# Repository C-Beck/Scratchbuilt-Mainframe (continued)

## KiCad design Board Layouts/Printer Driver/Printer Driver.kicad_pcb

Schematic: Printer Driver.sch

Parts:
C1, C2: 47p; C_Rect_L4.0mm_W2.5mm_P2.50mm
C3: 100n; C_Rect_L4.0mm_W2.5mm_P2.50mm
C4: 470u; CP_Radial_D8.0mm_P3.50mm
C5, C6, C7, C8: 10n; C_Rect_L4.0mm_W2.5mm_P2.50mm
D1, D2: LED; LED_D5.0mm
J1: USB_B; USB_B_OST_USB-B1HSxx_Horizontal
J2: Conn_01x06; PinHeader_1x06_P2.54mm_Vertical
J3: Conn_01x03; JST_VH_B3PS-VH_1x03_P3.96mm_Horizontal
J4: DB25_Female_MountingHoles; DSUB-25_Female_Horizontal_P2.77x2.84mm_EdgePinOffset9.90mm_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
J5: 8P8C; RJ45_Amphenol_54602-x08_Horizontal
R1: 4k7; R_Axial_DIN0207_L6.3mm_D2.5mm_P10.16mm_Horizontal
R2: 10k; R_Axial_DIN0207_L6.3mm_D2.5mm_P10.16mm_Horizontal
R3, R4: 27; R_Axial_DIN0207_L6.3mm_D2.5mm_P10.16mm_Horizontal
R5, R6: 270; R_Axial_DIN0207_L6.3mm_D2.5mm_P10.16mm_Horizontal
R7, R8: 2k; R_Axial_DIN0207_L6.3mm_D2.5mm_P10.16mm_Horizontal
R9, R11, R12, R14: 600; R_Axial_DIN0207_L6.3mm_D2.5mm_P10.16mm_Horizontal
R10, R13: 120; R_Axial_DIN0207_L6.3mm_D2.5mm_P10.16mm_Horizontal
U1: FT230XS; SSOP-16_3.9x4.9mm_P0.635mm
U2: PIC16F1503-IP; DIP-14_W7.62mm_Socket
U3: 74HC595; DIP-16_W7.62mm
U4: PCA9615; TSSOP-10_3x3mm_P0.5mm

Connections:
+5V: C4.1, C5.1, C6.1, C7.1, C8.1, J2.2, J3.1, R7.2, R8.2, R9.1, R12.1, U1.12 (VCC), U2.1 (VDD), U3.10 (~SRCLR), U3.16 (VCC), U4.1, U4.10
GND: C1.2, C2.2, C3.2, C4.2, C5.2, C6.2, C7.2, C8.2, J1.4 (GND), J2.3, J3.3, J4.18, J4.19, J4.20, J4.21, J4.22, J4.23, J4.24, J4.25, R2.2, R11.2, R14.2, U1.5 (GND), U1.13 (GND), U2.14 (VSS), U3.8 (GND), U3.13 (~OE), U4.5
unnamed: C1.1, J1.2 (D-), R3.2
unnamed: C2.1, J1.3 (D+), R4.2
unnamed: C3.1, D1.2 (A), D2.2 (A), U1.3 (VCCIO), U1.10 (3V3OUT), U1.11 (~RESET)
unnamed: D1.1 (K), R5.1
unnamed: D2.1 (K), R6.1
unnamed: J1.1 (VBUS), R1.1
unnamed: J2.1, U2.4 (RA3/T1G/CLC1IN0/~SS~/~MCLR~/Vpp)
unnamed: J2.4, J4.1, U2.13 (RA0/AN0/DACOUT1/C1IN+/ICSPDAT)
unnamed: J2.5, U1.1 (TXD), U2.12 (RA1/AN1/Vref+/C1IN0-/C2IN0-/ICSPCLK)
unnamed: J4.2, U3.15 (QA)
unnamed: J4.3, U3.1 (QB)
unnamed: J4.4, U3.2 (QC)
unnamed: J4.5, U3.3 (QD)
unnamed: J4.6, U3.4 (QE)
unnamed: J4.7, U3.5 (QF)
unnamed: J4.8, U3.6 (QG)
unnamed: J4.9, U3.7 (QH)
unnamed: J4.11, U2.5 (PWM1/CLC1/CWG1A/RC5)
unnamed: J5.1, R10.2, R11.1, U4.9
unnamed: J5.2, R9.2, R10.1, U4.8
unnamed: J5.7, R13.2, R14.1, U4.6
unnamed: J5.8, R12.2, R13.1, U4.7
unnamed: R1.2, R2.1, U1.16 (CBUS3)
unnamed: R3.1, U1.9 (USBDM)
unnamed: R4.1, U1.8 (USBDP)
unnamed: R5.2, U1.14 (CBUS1)
unnamed: R6.2, U1.7 (CBUS2)
unnamed: R7.1, U2.10 (SCK/SCL/CLC2/C2IN+/AN4/RC0), U4.4
unnamed: R8.1, U2.9 (SDI/SDA/PWM4/NCO1/C2IN1-/C1IN1-/AN5/RC1), U4.2
unnamed: U1.2 (~RTS), U2.3 (RA4/AN3/T1G/NCO1/SDO/CLKOUT)
unnamed: U1.4 (RXD), U2.11 (RA2/AN2/DACOUT2/C1OUT/T0CKI/~CWG1FLT~/C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)
unnamed: U1.6 (~CTS), U2.2 (RA5/T1CKI/NCO1CLK/CLCIN1/CLKIN)
unnamed: U2.6 (CLC2IN1/CWG1B/C2OUT/RC4), U3.12 (RCLK)
unnamed: U2.7 (~SS~/PWM2/CLCIN0/C2IN3-/C1IN3-/AN7/RC3), U3.11 (SRCLK)
unnamed: U2.8 (SDO/C2IN2-/C1IN2-/AN6/RC2), U3.14 (SER)

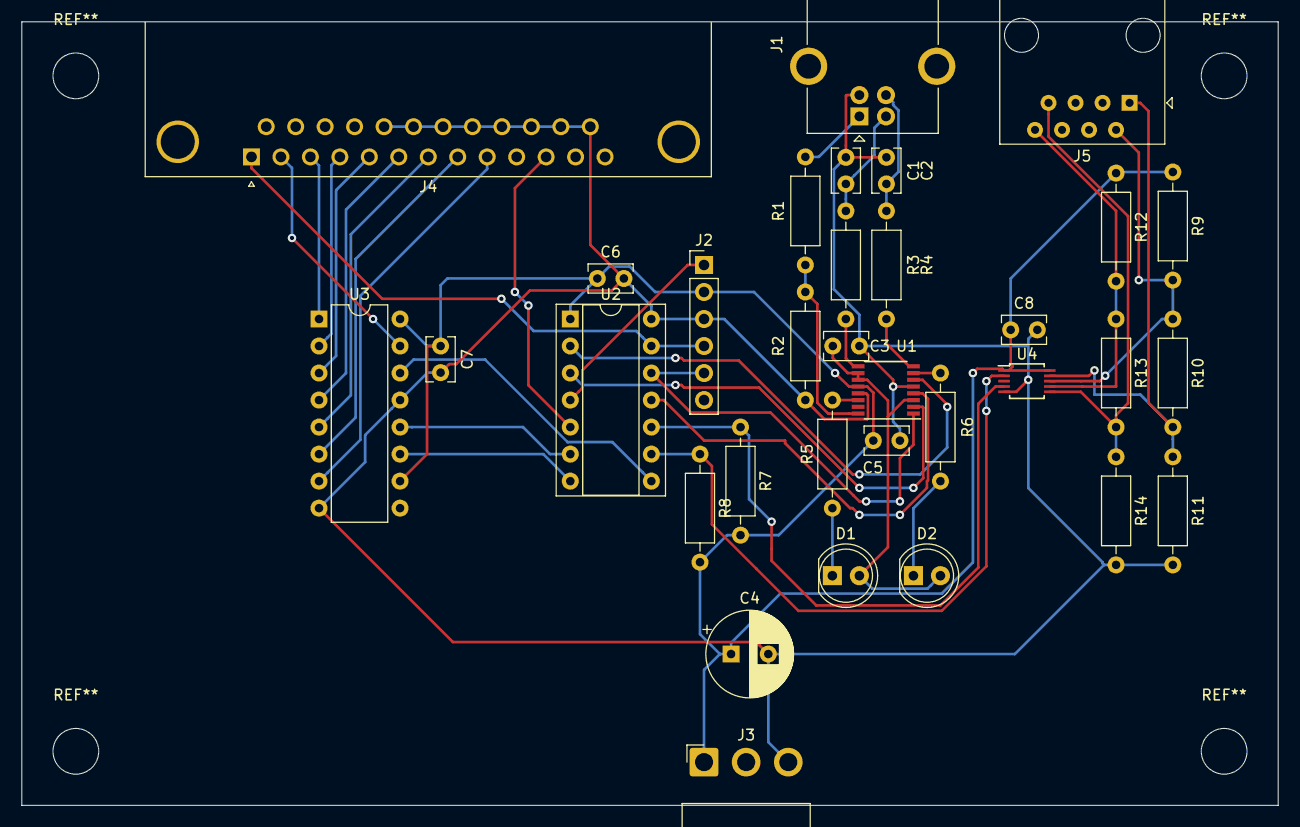
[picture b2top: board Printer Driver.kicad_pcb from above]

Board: 2 copper layers, 118.1 x 73.7 mm, 33 parts (0 on the bottom side), 37 nets.

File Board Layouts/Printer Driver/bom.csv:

Ref,Value,Desc,PN,Quantity,Price,Notes
"R1",4k7,"1/4 watt","CF14JT4K70CT-ND",1,"$0.10",
"R2",10k,"1/4 watt","CF14JT10K0CT-ND",1,"$0.10",
"R3,R4",27R,"1/4 watt","CF14JT27R0CT-ND",2,"$0.10",
"R5,R6",270R,"1/4 watt","CF14JT270RCT-ND",2,"$0.10",
"R7,R8",2k,"1/4 watt","CF14JT2K00CT-ND",2,"$0.10",
"R9,R11,R12,R14",600R,"1/4 watt",,4,,
"R10,R13",120R,"1/4 watt","CF14JT120RCT-ND",2,"$0.10",
"C1,C2",47p,"Ceramic","BC1009CT-ND",2,"$0.27",
"C3",100n,"Ceramic","BC5229CT-ND",1,"$0.23",
"C4",470u,"Polarized electrolytic","P5141-ND",1,"$0.10",
"C5,C6,C7,C8",10n,"Ceramic","BC5136-ND",4,"$0.21",
"D1,D2",,"5mm red led",,2,,
"U1","FT230XS","FTDI USB to Basic UART","768-1135-1-ND",1,"$2.04",
"U2","PIC16F1503-IP",,"PIC16F1503-I/P-ND",1,"$0.93",
"U3","74HC595","8-bit Serial-in Parallel-out Shift Register","296-1600-5-ND",1,"$0.53",
"U4","PCA9615","Differential I2C Bus buffer","568-11484-1-ND",1,"$2,95",
"J1",,"USB type B Female",,1,,
"J2",,"1x6 .1'' male header",,1,,
"J3",,"1x3 Power connector",,1,,
"J4",,"8p8c female",,1,,
"J5",,"Dsub-25 female w/ mounting holes",,1,,

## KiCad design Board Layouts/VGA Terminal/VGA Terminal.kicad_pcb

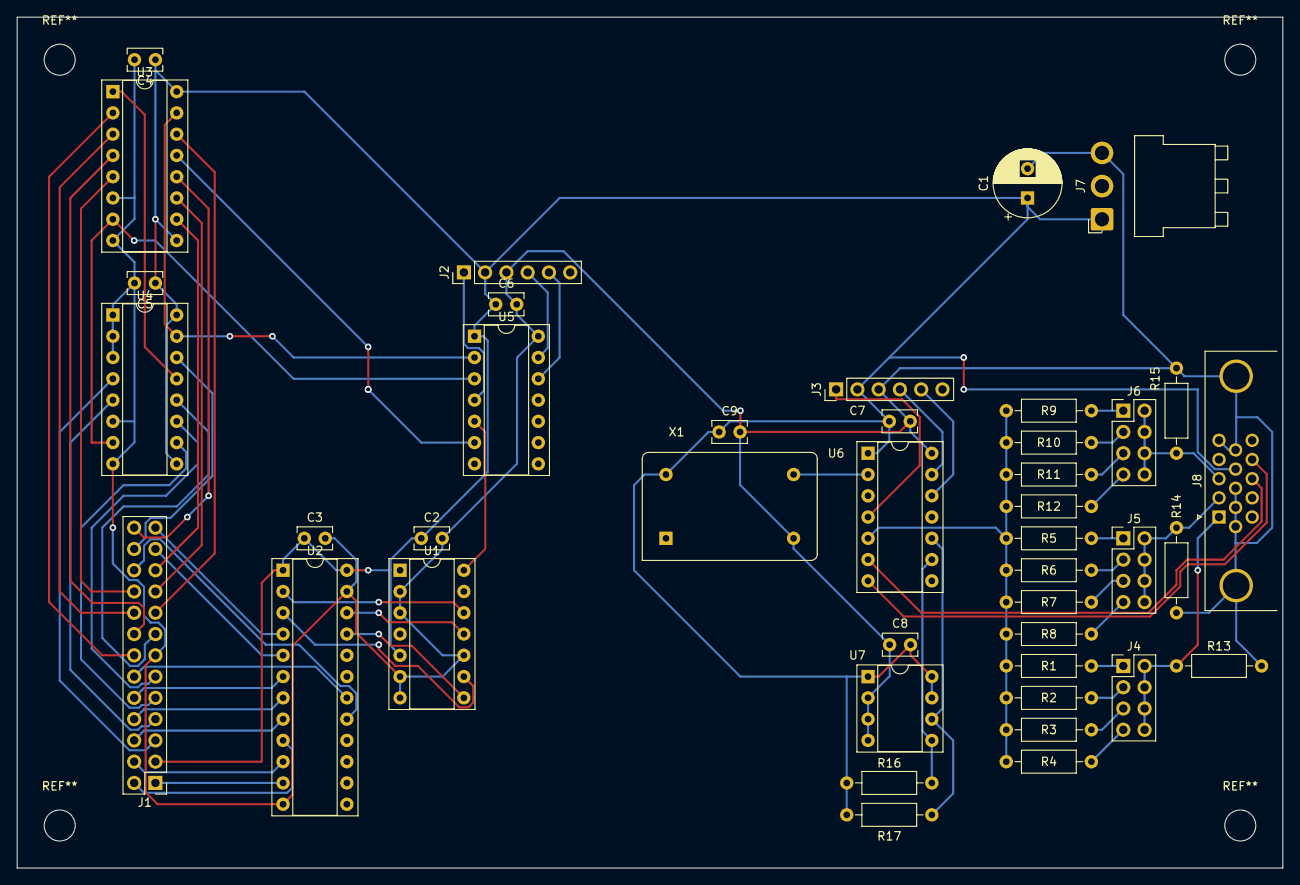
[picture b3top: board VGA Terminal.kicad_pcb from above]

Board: 2 copper layers, 151.1 x 101.6 mm, 42 parts (0 on the bottom side), 62 nets.

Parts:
C1: 470u; CP_Radial_D8.0mm_P3.50mm
C2, C3, C4, C5, C6, C7, C8, C9: 10n; C_Rect_L4.0mm_W2.5mm_P2.50mm
J1: Conn_02x13_Odd_Even; PinHeader_2x13_P2.54mm_Vertical
J2, J3: Conn_01x06; PinHeader_1x06_P2.54mm_Vertical
J4, J5, J6: Conn_02x04_Odd_Even; PinHeader_2x04_P2.54mm_Vertical
J7: Conn_01x03; JST_VH_B3PS-VH_1x03_P3.96mm_Horizontal
J8: DB15_Female_HighDensity_MountingHoles; DSUB-15-HD_Male_Horizontal_P2.29x1.98mm_EdgePinOffset3.03mm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
R1, R5, R9: 3k9; R_Axial_DIN0207_L6.3mm_D2.5mm_P10.16mm_Horizontal
R2, R6, R10: 2k2; R_Axial_DIN0207_L6.3mm_D2.5mm_P10.16mm_Horizontal
R3, R7, R11: 1k; R_Axial_DIN0207_L6.3mm_D2.5mm_P10.16mm_Horizontal
R4, R8, R12: 470; R_Axial_DIN0207_L6.3mm_D2.5mm_P10.16mm_Horizontal
R13, R14, R15: 75; R_Axial_DIN0207_L6.3mm_D2.5mm_P10.16mm_Horizontal
R16, R17: 2k; R_Axial_DIN0207_L6.3mm_D2.5mm_P10.16mm_Horizontal
U1: 74LS90; DIP-14_W7.62mm_Socket
U2: 74HC4514; DIP-24_W7.62mm_Socket
U3, U4: 74LS166; DIP-16_W7.62mm_Socket
U5: PIC16F1503-IP; DIP-14_W7.62mm_Socket
U6: PIC16LF1554-IP; DIP-14_W7.62mm_Socket
U7: 24LC16; DIP-8_W7.62mm_Socket
X1: 25.175 MHz; Oscillator_DIP-14

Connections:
+5V: C1.1, C2.1, C3.1, C4.1, C5.1, C6.1, C7.1, C8.1, C9.1, J1.3, J2.2, J3.2, J7.1, J8.9, R16.1, R17.1, U1.5, U2.1, U2.24, U3.9, U3.16, U4.9, U4.16, U5.1, U6.1, U7.1, U7.7, U7.8, X1.14
/HSync: J8.13, U6.6
/KBD-CAPL: J1.5, U4.4
/KBD-CAPS: J1.9, U4.10
/KBD-CTL: J1.11, U4.11
/KBD-OAPL: J1.7, U4.5
/KBD-RST: J1.15, U4.12
/KBD-SHFT: J1.24, U4.14
/KBD-X0: J1.14, U3.2
/KBD-X1: J1.18, U3.3
/KBD-X2: J1.16, U3.4
/KBD-X3: J1.20, U3.5
/KBD-X4: J1.21, U3.10
/KBD-X5: J1.19, U3.11
/KBD-X6: J1.26, U3.12
/KBD-X7: J1.17, U3.14
/KBD-Y0: J1.1, U2.11
/KBD-Y1: J1.2, U2.9
/KBD-Y2: J1.4, U2.10
/KBD-Y3: J1.6, U2.8
/KBD-Y4: J1.8, U2.7
/KBD-Y5: J1.10, U2.6
/KBD-Y6: J1.23, U2.5
/KBD-Y7: J1.25, U2.4
/KBD-Y8: J1.12, U2.18
/KBD-Y9: J1.22, U2.17
/VSync: J8.14, U6.7
/Video: R1.2, R2.2, R3.2, R4.2, R5.2, R6.2, R7.2, R8.2, R9.2, R10.2, R11.2, R12.2, U6.5
GND: C1.2, C2.2, C3.2, C4.2, C5.2, C6.2, C7.2, C8.2, C9.2, J1.13, J2.3, J3.3, J7.3, J8.0, J8.5, J8.6, J8.7, J8.8, J8.10, R13.2, R14.2, R15.2, U1.2, U1.3, U1.6, U1.7, U1.10, U2.12, U2.23, U3.6, U3.8, U4.1, U4.2, U4.3, U4.6, U4.8, U5.14, U6.14, U7.2, U7.3, U7.4, X1.7
unnamed: J2.1, U5.4
unnamed: J2.4, U5.13
unnamed: J2.5, U5.12
unnamed: J3.1, U6.4
unnamed: J3.4, U6.13
unnamed: J3.5, U6.12
unnamed: J4.1, R1.1
unnamed: J4.2, J4.4, J4.6, J4.8, J8.1, R13.1
unnamed: J4.3, R2.1
unnamed: J4.5, R3.1
unnamed: J4.7, R4.1
unnamed: J5.1, R5.1
unnamed: J5.2, J5.4, J5.6, J5.8, J8.2, R14.1
unnamed: J5.3, R6.1
unnamed: J5.5, R7.1
unnamed: J5.7, R8.1
unnamed: J6.1, R9.1
unnamed: J6.2, J6.4, J6.6, J6.8, J8.3, R15.1
unnamed: J6.3, R10.1
unnamed: J6.5, R11.1
unnamed: J6.7, R12.1
unnamed: R16.2, U6.9, U7.5
unnamed: R17.2, U6.10, U7.6
unnamed: U1.8, U2.21
unnamed: U1.9, U2.3
unnamed: U1.11, U2.22
unnamed: U1.12, U2.2
unnamed: U1.14, U5.5
unnamed: U3.1, U4.13
unnamed: U3.7, U4.7, U5.3
unnamed: U3.13, U5.6
unnamed: U3.15, U4.15, U5.2
unnamed: U6.2, X1.8

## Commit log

2019-01-20 :lollipop: Added .gitattributes
2019-01-20 Add printer driver code
2019-01-20 Create LICENSE
2019-01-20 Update issue templates
2019-01-20 Starting Documentation
2019-01-20 Writing Documentation
2019-01-22 Documentation Writing and Adding Bibliography File
2019-01-30 Writing Docs
2019-03-04 Documentaion: adding interface specs
2019-03-23 Started work on the schematics and pcb layouts
2019-03-24 Working on schematics and board layouts
2019-03-24 Working on board layouts and schematics
2019-03-28 Working on schematics
2019-03-28 Add *.bak and *.kicad_pcb-bak files
2019-03-28 Trying to fix lang id
2019-03-28 Revert change
2019-03-30 Working on schematics and board routing
2019-04-01 Routed pcb added bom for printer driver
2019-04-05 Writing documentation renamed a bunch of stuff
2019-04-06 Documentation writing
2019-04-07 Added hex decoders to front panel
2019-07-21 Adding a schematic for a terminal using a CGA monitor
2019-07-26 Working on CGA terminal
2019-07-29 Added code to generate flowcharts
2019-09-09 Started work on 300bps modem
2020-08-10 Update local changes & working on printer driver
2020-08-10 Added comments
2020-08-24 Added LUT for hiragana started input parsing
